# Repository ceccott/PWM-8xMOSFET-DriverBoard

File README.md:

# PWM 8x MOSFET Driver Board
Opto-insulated current limited 8 channel MOSFET power driver board PCB

### Schematic 

### Board

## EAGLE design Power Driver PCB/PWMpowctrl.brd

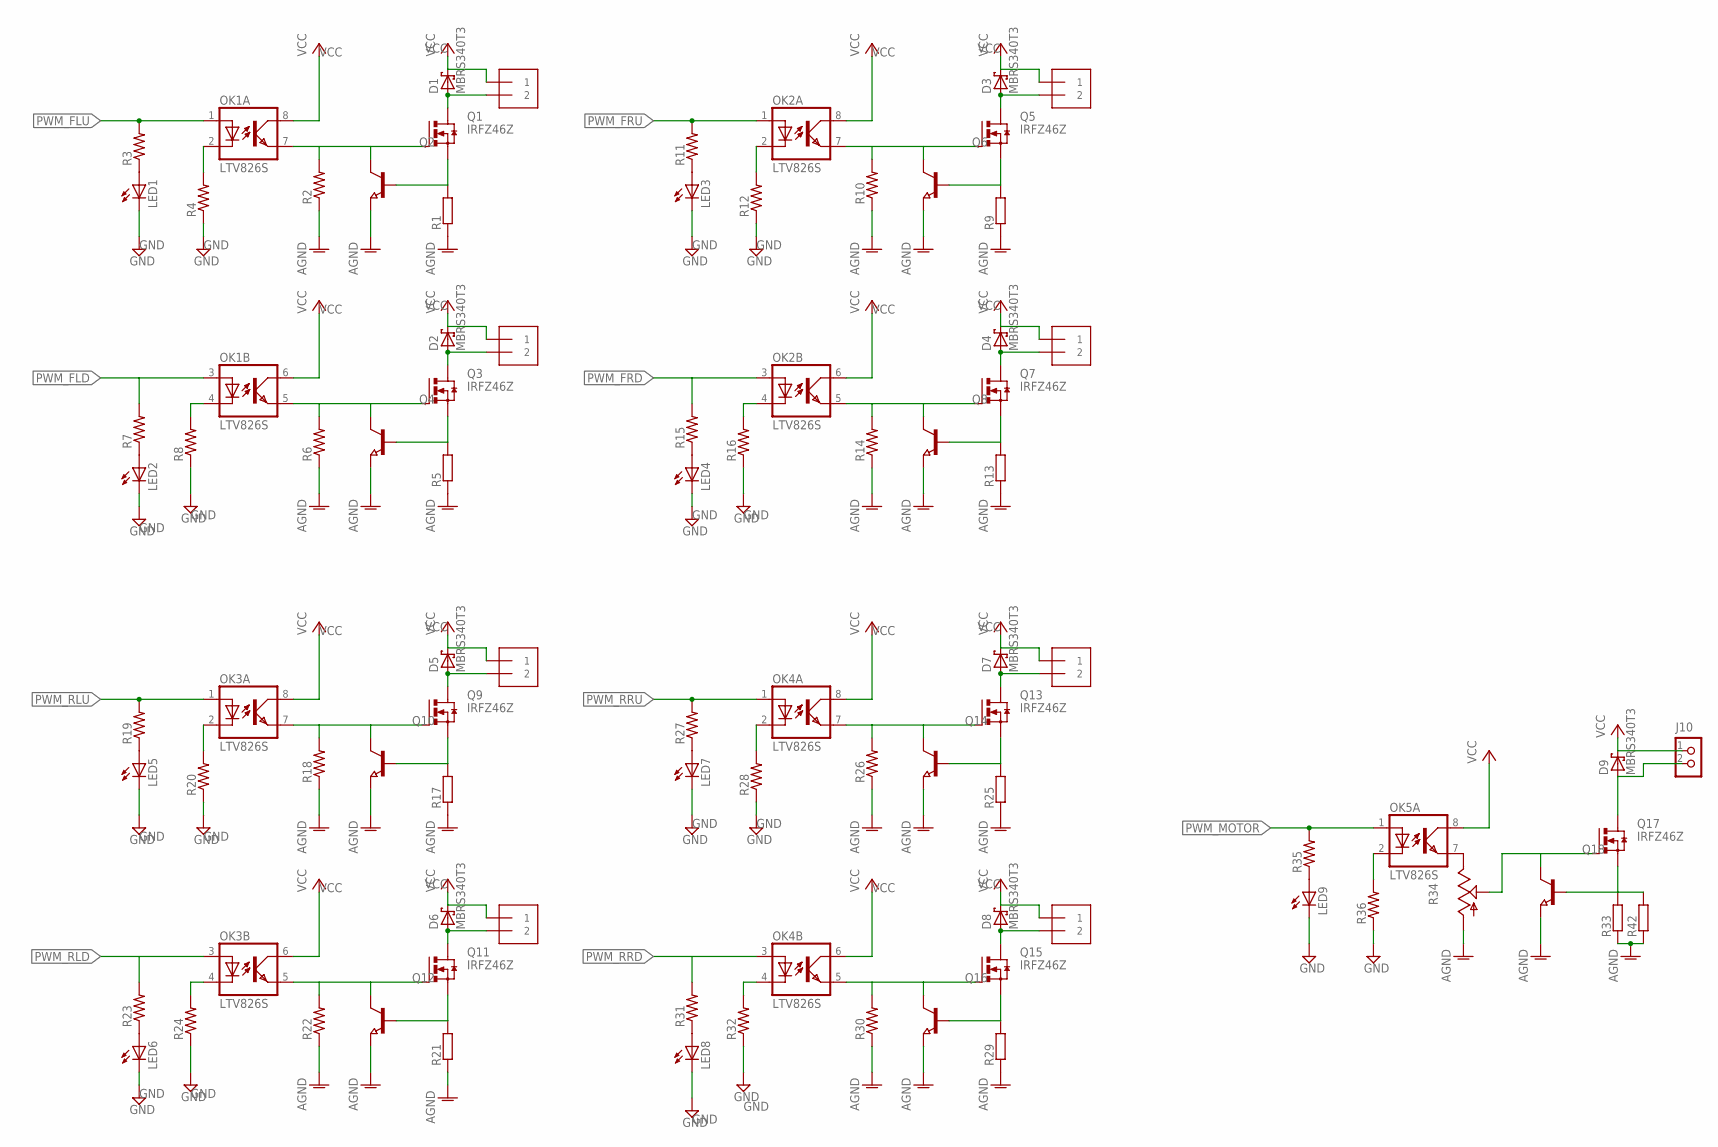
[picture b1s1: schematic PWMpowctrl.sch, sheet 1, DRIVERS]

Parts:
D1, D2, D3, D4, D5, D6, D7, D8, D9: MBRS340T3; SMC
J1, J2, J3, J4, J5, J6, J7, J8: 1X2-3.5MM; 3.5MMTERM
J10: CON_TERMINAL_BLOCK_02-5MM; TERMINAL_BLOCK_2P_5
LED1, LED2, LED3, LED4, LED5, LED6, LED7, LED8, LED9: LED3MM
OK1, OK2, OK3, OK4, OK5: LTV826S; DIL8-SMD
Q1, Q3, Q5, Q7, Q9, Q11, Q13, Q15, Q17: IRFZ46Z; D2PACK
Q2, Q4, Q6, Q8, Q10, Q12, Q14, Q16, Q18: NPN-TRANSISTOR_SOT23; SOT23
R1, R5, R9, R13, R17, R21, R25, R29, R33, R42: BVS
R2, R3, R4, R6, R7, R8, R10, R11, R12, R14, R15, R16, R18, R19, R20, R22, R23, R24, R26, R27, R28, R30, R31, R32, R35, R36: R-US_M1206; M1206
R34: TRIM_US-CA6V; CA6V

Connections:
AGND: Q2.2 (E), Q4.2 (E), Q6.2 (E), Q8.2 (E), Q10.2 (E), Q12.2 (E), Q14.2 (E), Q16.2 (E), Q18.2 (E), R1.2, R2.1, R5.2, R6.1, R9.2, R10.1, R13.2, R14.1, R17.2, R18.1, R21.2, R22.1, R25.2, R26.1, R29.2, R30.1, R33.2, R42.2; also elsewhere on the board
GND: LED1.K (C), LED2.K (C), LED3.K (C), LED4.K (C), LED5.K (C), LED6.K (C), LED7.K (C), LED8.K (C), LED9.K (C), R4.1, R8.1, R12.1, R16.1, R20.1, R24.1, R28.1, R32.1, R36.1
unnamed: Q1.3 (S), Q2.1 (B), R1.1
unnamed: Q17.3 (S), Q18.1 (B), R33.1, R42.1
unnamed: OK1.2 (C), R4.2
unnamed: Q3.3 (S), Q4.1 (B), R5.1
unnamed: OK1.7 (EMIT), Q1.1 (G), Q2.3 (C), R2.2
unnamed: D1.A, J1.2, Q1.2 (D)
unnamed: OK1.5 (EMIT), Q3.1 (G), Q4.3 (C), R6.2
unnamed: LED1.A, R3.1
unnamed: D2.A, J2.2, Q3.2 (D)
unnamed: LED2.A, R7.1
unnamed: OK1.4 (C), R8.2
unnamed: Q17.1 (G), Q18.3 (C), R34.S
unnamed: Q5.3 (S), Q6.1 (B), R9.1
unnamed: OK2.7 (EMIT), Q5.1 (G), Q6.3 (C), R10.2
unnamed: D3.A, J3.2, Q5.2 (D)
unnamed: LED3.A, R11.1
unnamed: D9.A, J10.2, Q17.2 (D)
unnamed: OK2.2 (C), R12.2
unnamed: Q7.3 (S), Q8.1 (B), R13.1
unnamed: OK2.5 (EMIT), Q7.1 (G), Q8.3 (C), R14.2
unnamed: D4.A, J4.2, Q7.2 (D)
unnamed: LED4.A, R15.1
unnamed: OK2.4 (C), R16.2
unnamed: LED9.A, R35.1
unnamed: Q9.3 (S), Q10.1 (B), R17.1
unnamed: OK3.7 (EMIT), Q9.1 (G), Q10.3 (C), R18.2
unnamed: D5.A, J5.2, Q9.2 (D)
unnamed: LED5.A, R19.1
unnamed: OK5.2 (C), R36.2
unnamed: OK3.2 (C), R20.2
unnamed: Q11.3 (S), Q12.1 (B), R21.1
unnamed: OK3.5 (EMIT), Q11.1 (G), Q12.3 (C), R22.2
unnamed: D6.A, J6.2, Q11.2 (D)
unnamed: LED6.A, R23.1
unnamed: OK3.4 (C), R24.2
unnamed: Q13.3 (S), Q14.1 (B), R25.1
unnamed: OK4.7 (EMIT), Q13.1 (G), Q14.3 (C), R26.2
unnamed: D7.A, J7.2, Q13.2 (D)
unnamed: LED7.A, R27.1
unnamed: OK4.2 (C), R28.2
unnamed: Q15.3 (S), Q16.1 (B), R29.1
unnamed: OK4.5 (EMIT), Q15.1 (G), Q16.3 (C), R30.2
unnamed: D8.A, J8.2, Q15.2 (D)
unnamed: LED8.A, R31.1
unnamed: OK4.4 (C), R32.2
unnamed: OK5.7 (EMIT), R34.E
PWM_FLD: OK1.3 (A), R7.2; also elsewhere on the board
PWM_FLU: OK1.1 (A), R3.2; also elsewhere on the board
PWM_FRD: OK2.3 (A), R15.2; also elsewhere on the board
PWM_FRU: OK2.1 (A), R11.2; also elsewhere on the board
PWM_MOTOR: OK5.1 (A), R35.2; also elsewhere on the board
PWM_RLD: OK3.3 (A), R23.2; also elsewhere on the board
PWM_RLU: OK3.1 (A), R19.2; also elsewhere on the board
PWM_RRD: OK4.3 (A), R31.2; also elsewhere on the board
PWM_RRU: OK4.1 (A), R27.2; also elsewhere on the board
VCC: D1.C, D2.C, D3.C, D4.C, D5.C, D6.C, D7.C, D8.C, D9.C, J1.1, J2.1, J3.1, J4.1, J5.1, J6.1, J7.1, J8.1, J10.1, OK1.6 (COL), OK1.8 (COL), OK2.6 (COL), OK2.8 (COL), OK3.6 (COL), OK3.8 (COL), OK4.6 (COL), OK4.8 (COL), OK5.8 (COL); also elsewhere on the board

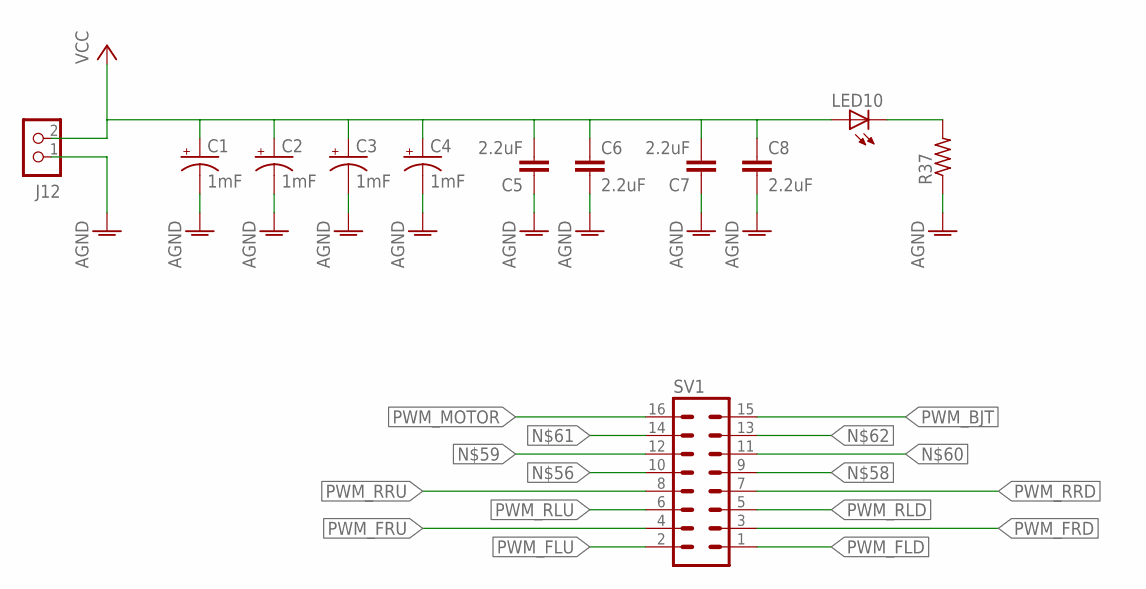
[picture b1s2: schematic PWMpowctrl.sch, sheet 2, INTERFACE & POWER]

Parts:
C1, C2, C3, C4: 1mF; CPOL-RADIAL-5MM-10MM
C5, C6, C7, C8: 2.2uF; 1206
J12: CON_TERMINAL_BLOCK_02-5MM; TERMINAL_BLOCK_2P_5
LED10: LED5MM
R37: R-US_M1206; M1206
SV1: MA08-2

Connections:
AGND: C1.-, C2.-, C3.-, C4.-, C5.1, C6.2, C7.1, C8.2, J12.1, R37.1; also elsewhere on the board
unnamed: LED10.K (C), R37.2
PWM_BJT: SV1.15
PWM_FLD: SV1.1; also elsewhere on the board
PWM_FLU: SV1.2; also elsewhere on the board
PWM_FRD: SV1.3; also elsewhere on the board
PWM_FRU: SV1.4; also elsewhere on the board
PWM_MOTOR: SV1.16; also elsewhere on the board
PWM_RLD: SV1.5; also elsewhere on the board
PWM_RLU: SV1.6; also elsewhere on the board
PWM_RRD: SV1.7; also elsewhere on the board
PWM_RRU: SV1.8; also elsewhere on the board
VCC: C1.+, C2.+, C3.+, C4.+, C5.2, C6.1, C7.2, C8.1, J12.2, LED10.A; also elsewhere on the board

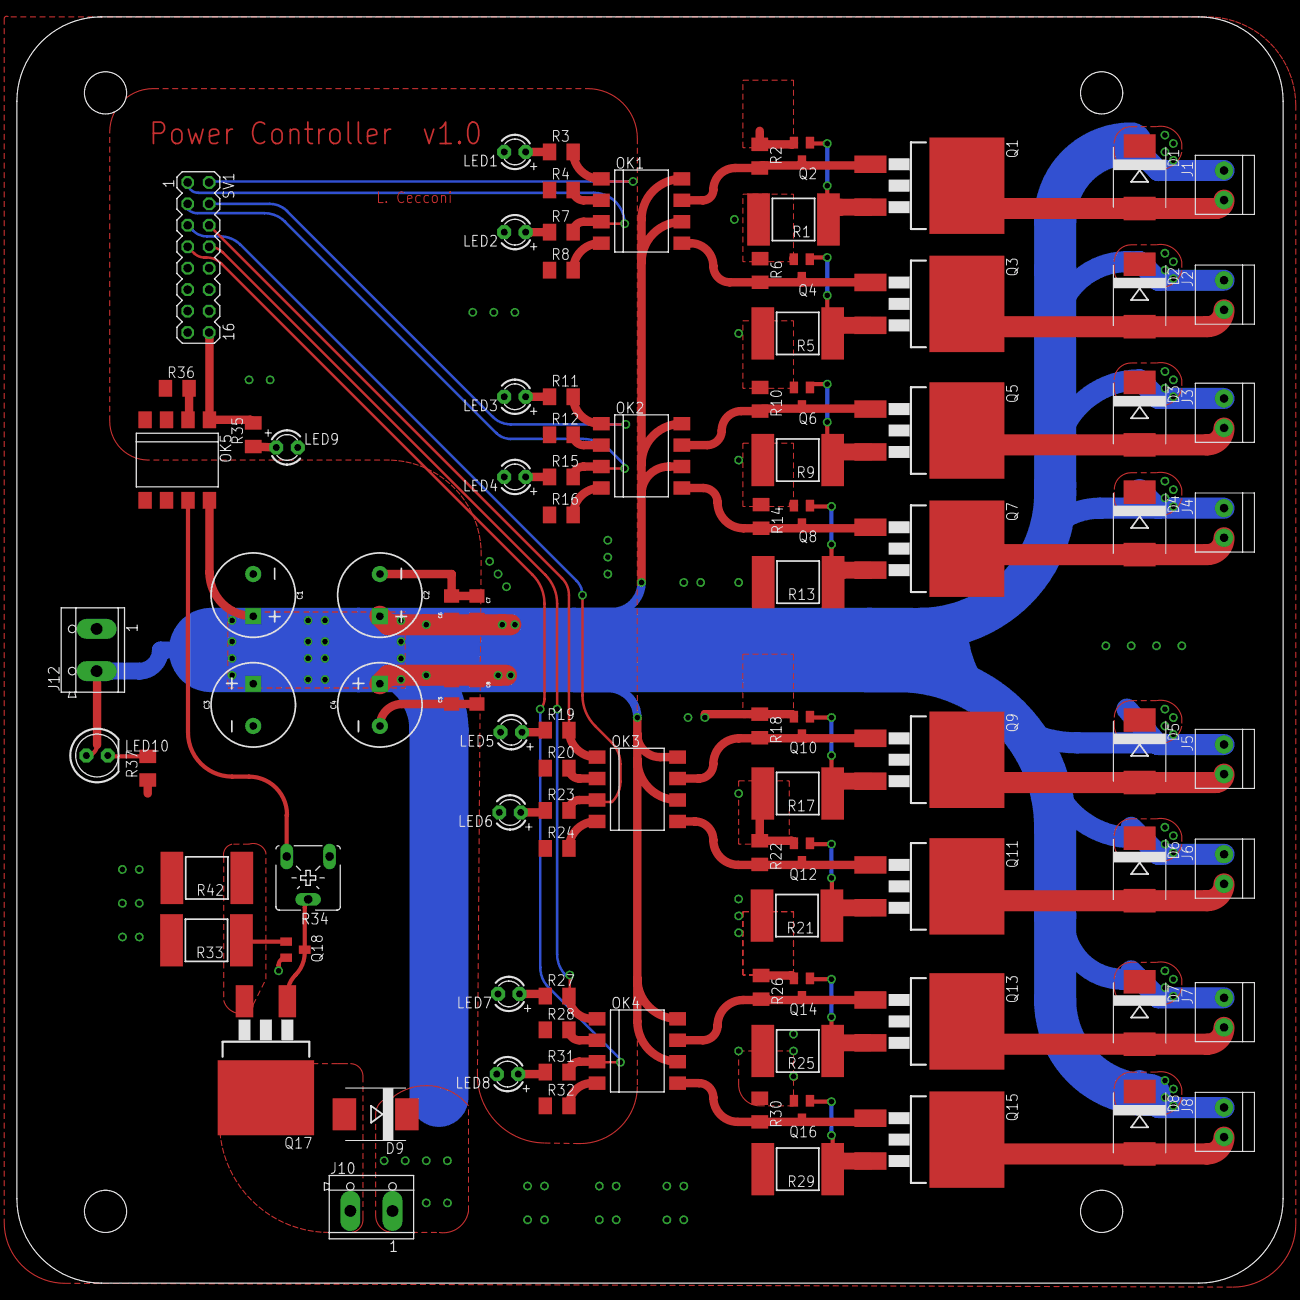
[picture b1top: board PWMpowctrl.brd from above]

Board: 2 copper layers, 150.0 x 150.0 mm, 99 parts (0 on the bottom side), 59 nets.

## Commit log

2019-09-06 init repo

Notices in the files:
parts and their libraries:
SparkFun-Capacitors: Licensing: Creative Commons ShareAlike 4.0 International - https://creativecommons.org/licenses/by-sa/4.0
